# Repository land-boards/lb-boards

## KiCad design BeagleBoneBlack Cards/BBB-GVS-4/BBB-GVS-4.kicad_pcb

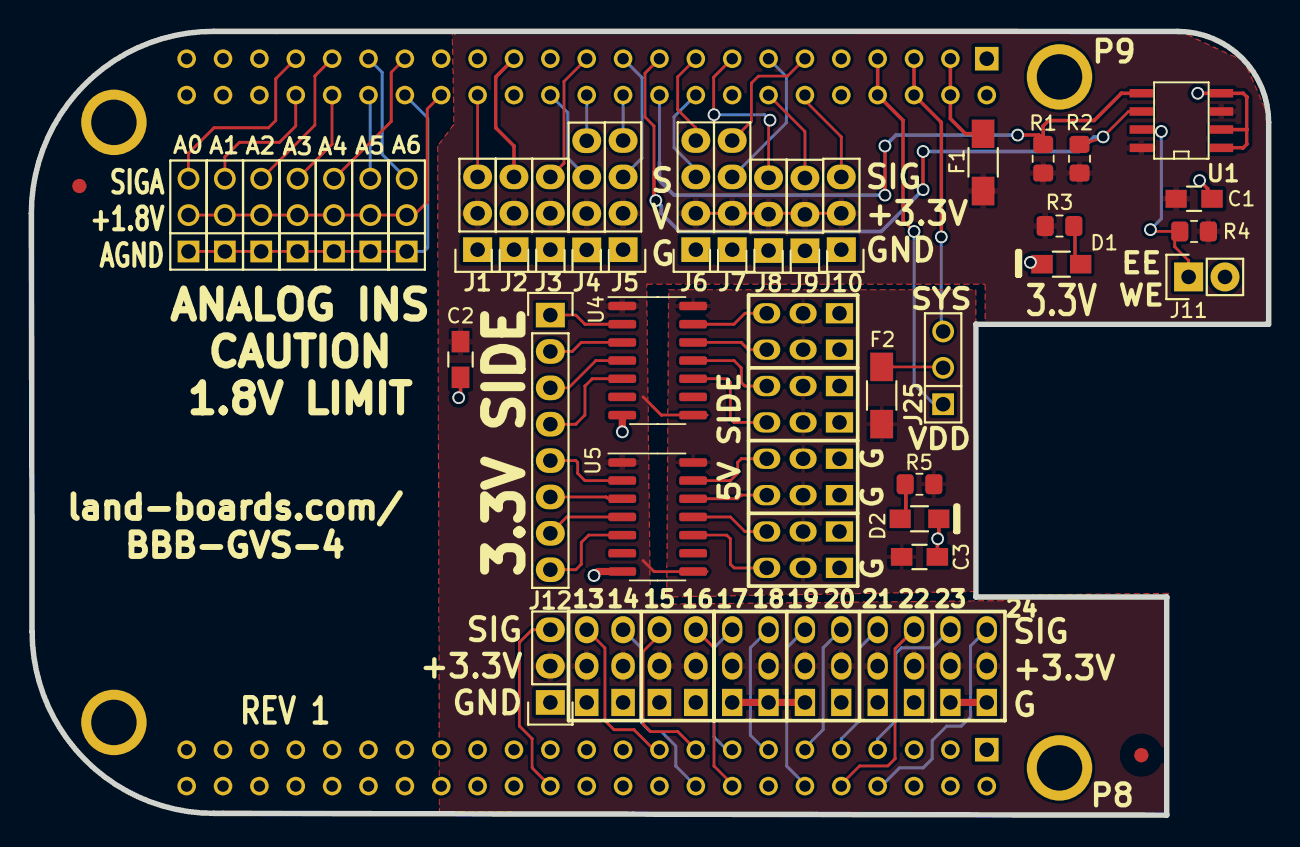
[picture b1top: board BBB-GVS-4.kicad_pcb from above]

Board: 2 copper layers, 86.4 x 54.7 mm, 43 parts (1 on the bottom side), 64 nets.

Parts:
A0, A1, A2, A3, A4, A5, A6: CONN_3; PIN_ARRAY_3X1
BRD1: BEAGLEBONE
C1: 1uF; C_0805_HandSoldering
C2, C3: 104; C_0805_HandSoldering
D1, D2: LED; R_0805_HandSoldering
F1, F2: FUSE; C_1206_HandSoldering
FID1, FID2: CONN_1; FIDUCIAL
J1, J2, J3, J8, J9, J10, J12: CONN_3; Pin_Header_Straight_1x03
J4, J5, J6, J7: CONN_4; Pin_Header_Straight_1x04
J11: CONN_2; Pin_Header_Straight_1x02
J16: GVS-4X3; Pin_Header_Straight_3x04
J24, J26: GVS-8X3; Pin_Header_Straight_3x08
J25: CONN_3; PIN_ARRAY_3X1
P1: CONN_8; Pin_Header_Straight_1x08
R1, R2, R4: 5.6K; R_0805_2012Metric_Pad1.20x1.40mm_HandSolder
R3: 120; R_0805_2012Metric_Pad1.20x1.40mm_HandSolder
R5: 330; R_0805_2012Metric_Pad1.20x1.40mm_HandSolder
TESTED: COUPON; REV_BLOCK
U1: I2C-EEPROM; SO8E-wider
U4, U5: TXS0104; SO-14_3.9x8.65mm_P1.27mm

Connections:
/BBB EEPROM Power Etc/F5VDD: F2.2, J25.2 (PM)
/P8 Connector/EHRPWM2A: BRD1.B19 (EHRPWM2A), J16.3
/P8 Connector/EHRPWM2B: BRD1.B13 (EHRPWM2B), J24.6
/P8 Connector/GPIO0_27: BRD1.B17 (GPIO0_27), J16.9
/P8 Connector/GPIO1_12: BRD1.B12 (GPIO1_12), J24.9
/P8 Connector/GPIO1_13: BRD1.B11 (GPIO1_13), J24.12
/P8 Connector/GPIO1_14: BRD1.B16 (GPIO1_14), J16.12
/P8 Connector/GPIO1_15: BRD1.B15 (GPIO1_15), J24.3
/P8 Connector/GPIO1_29: BRD1.B26 (GPIO1_29), J12.3
/P8 Connector/GPIO2_1: BRD1.B18 (GPIO2_1), J16.6
/P8 Connector/TIMER4: BRD1.B7 (TIMER4), J24.21
/P8 Connector/TIMER5: BRD1.B9 (TIMER5), J24.15
/P8 Connector/TIMER6: BRD1.B10 (TIMER6), J24.18
/P8 Connector/TIMER7: BRD1.B8 (TIMER7), J24.24
/P9 Connector/EHRPWM1A: BRD1.C14 (EHRPWM1A), J9.3
/P9 Connector/GPIO1_16: BRD1.C15 (GPIO1_16), J8.3
/P9 Connector/GPIO1_17: BRD1.C23 (GPIO1_17), J3.3
/P9 Connector/GPIO1_28: BRD1.C12 (GPIO1_28), J10.3
/P9 Connector/GPIO3_19: BRD1.C27 (GPIO3_19), J2.3
/P9 Connector/I2C1_SCL: BRD1.C17 (I2C1_SCL), J6.4
/P9 Connector/I2C1_SDA: BRD1.C18 (I2C1_SDA), J6.3
/P9 Connector/SPI1_D1: BRD1.C30 (SPI1_D1), J1.3
/P9 Connector/UART1_RXD: BRD1.C26 (UART1_RXD), J4.3
/P9 Connector/UART1_TXD: BRD1.C24 (UART1_TXD), J4.4
/P9 Connector/UART2_RXD: BRD1.C22 (UART2_RXD), J5.4
/P9 Connector/UART2_TXD: BRD1.C21 (UART2_TXD), J5.3
/P9 Connector/UART4_RXD: BRD1.C11 (UART4_RXD), J7.4
/P9 Connector/UART4_TXD: BRD1.C13 (UART4_TXD), J7.3
AIN0: A0.3, BRD1.C39 (AIN0)
AIN1: A1.3, BRD1.C40 (AIN1)
AIN2: A2.3, BRD1.C37 (AIN2)
AIN3: A3.3, BRD1.C38 (AIN3)
AIN4: A4.3, BRD1.C33 (AIN4)
AIN5: A5.3, BRD1.C36 (AIN5)
AIN6: A6.3, BRD1.C35 (AIN6)
GND: BRD1.B1 (DGND), BRD1.B2 (DGND), BRD1.C1 (DGND), BRD1.C2 (DGND), BRD1.C43 (DGND), BRD1.C44 (DGND), BRD1.C45 (DGND), BRD1.C46 (DGND), C1.2, C2.2, C3.2, D1.2 (K), D2.2 (K), J1.1, J2.1, J3.1, J4.1, J5.1, J6.1, J7.1, J8.1, J9.1, J10.1, J11.2 (PM), J12.1, J16.1 (G), J16.4, J16.7, J16.10, J24.1 (G), J24.4, J24.7, J24.10, J24.13, J24.16, J24.19, J24.22, J26.1 (G), J26.4, J26.7, J26.10, J26.13, J26.16, J26.19, J26.22, U1.1 (A0), U1.2 (A1), U1.4 (GND), U4.7 (GND), U5.7 (GND)
GNDA_ADC: A0.1, A1.1, A2.1, A3.1, A4.1, A5.1, A6.1, BRD1.C34 (GNDA_ADC)
I2C2_SCL: BRD1.C19 (I2C2_SCL), R2.2, U1.6 (SCL)
I2C2_SDA: BRD1.C20 (I2C2_SDA), R1.2, U1.5 (SDA)
unnamed: D1.1 (A), R3.2
unnamed: D2.1 (A), R5.2
unnamed: J11.1, R4.2, U1.7 (WP)
unnamed: J26.3, U5.10 (B4)
unnamed: J26.6, U5.11 (B3)
unnamed: J26.9, U5.12 (B2)
unnamed: J26.12, U5.13 (B1)
unnamed: J26.15, U4.10 (B4)
unnamed: J26.18, U4.11 (B3)
unnamed: J26.21, U4.12 (B2)
unnamed: J26.24, U4.13 (B1)
unnamed: P1.1, U4.2 (A1)
unnamed: P1.2, U4.3 (A2)
unnamed: P1.3, U4.4 (A3)
unnamed: P1.4, U4.5 (A4)
unnamed: P1.5, U5.2 (A1)
unnamed: P1.6, U5.3 (A2)
unnamed: P1.7, U5.4 (A3)
unnamed: P1.8, U5.5 (A4)
SYS_5V: BRD1.C7 (SYS_5V), BRD1.C8 (SYS_5V), J25.1
VCC_3V3EXP: C1.1, C2.1, F1.1, J1.2 (PM), J2.2 (PM), J3.2 (PM), J4.2, J5.2, J6.2, J7.2, J8.2 (PM), J9.2 (PM), J10.2 (PM), J12.2 (PM), J16.2 (V), J16.5, J16.8, J16.11, J24.2 (V), J24.5, J24.8, J24.11, J24.14, J24.17, J24.20, J24.23, R1.1, R2.1, R3.1, R4.1, U1.3 (A2), U1.8 (VCC), U4.1 (VCCA(LV)), U4.8 (OE), U5.1 (VCCA(LV)), U5.8 (OE)
VDD_3V3-UF: BRD1.C3 (VDD_3V3EXP), BRD1.C4 (VDD_3V3EXP), F1.2
VDD_5V: C3.1, F2.1, J26.2 (V), J26.5, J26.8, J26.11, J26.14, J26.17, J26.20, J26.23, R5.1, U4.14 (VCCB(HV)), U5.14 (VCCB(HV))
VDD_5V-UF: BRD1.C5 (VDD_5V), BRD1.C6 (VDD_5V), J25.3
VDD_ADC: A0.2 (PM), A1.2 (PM), A2.2 (PM), A3.2 (PM), A4.2 (PM), A5.2 (PM), A6.2 (PM), BRD1.C32 (VDD_ADC)

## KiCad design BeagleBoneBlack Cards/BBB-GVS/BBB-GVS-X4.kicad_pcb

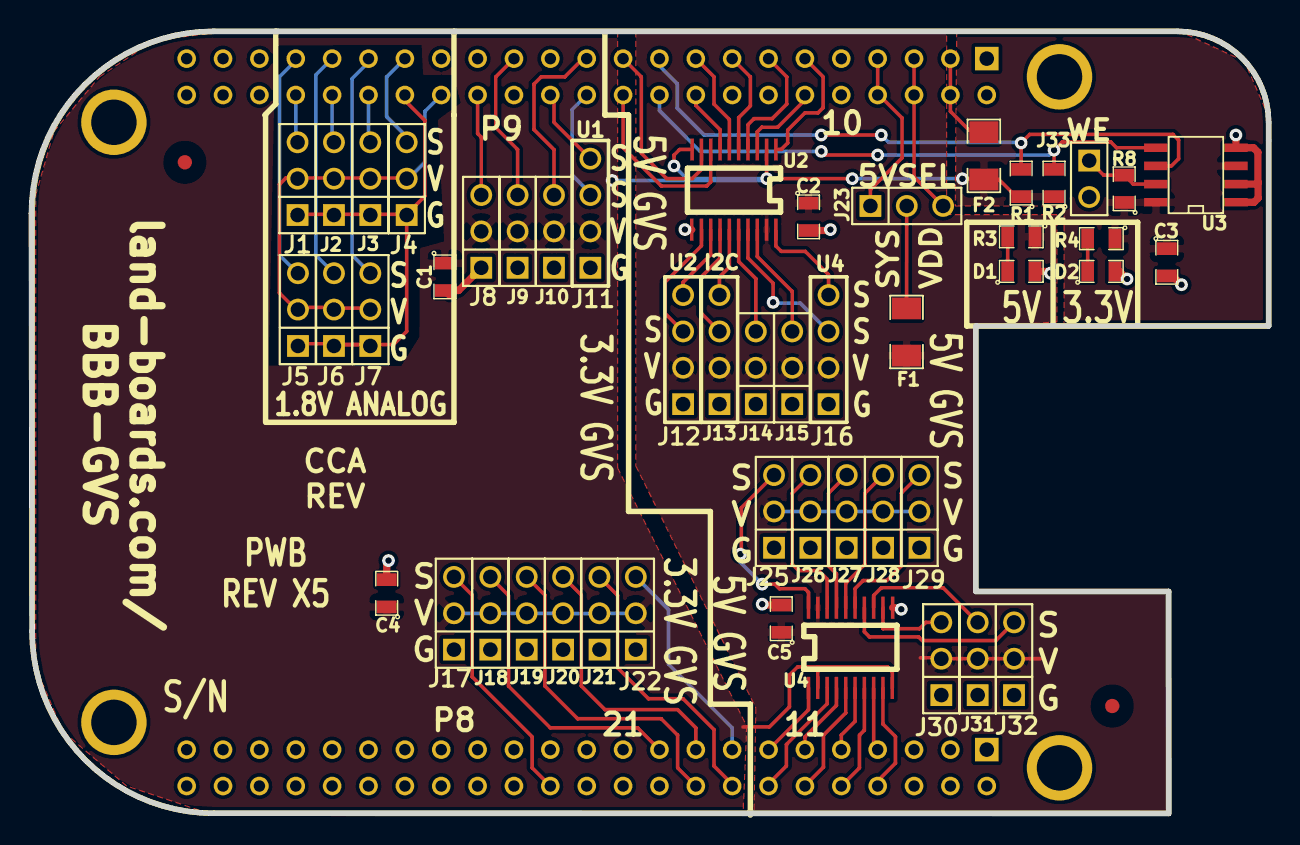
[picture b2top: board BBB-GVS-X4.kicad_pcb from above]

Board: 2 copper layers, 86.4 x 54.6 mm, 52 parts (0 on the bottom side), 64 nets.

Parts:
BRD1: BEAGLEBONE
C1, C2, C4, C5: 104; SM0805
C3: 1uF; SM0805
D1, D2: LED; SM0805
F1, F2: FUSE; SM1206
FID1, FID2: CONN_1; FIDUCIAL
J1, J2, J3, J4, J5, J6, J7, J8, J9, J10, J14, J15, J17, J18, J19, J20, J21, J22, J23, J25, J26, J27, J28, J29, J30, J31, J32: CONN_3; PIN_ARRAY_3X1
J11, J12, J13, J16: CONN_4; PIN_ARRAY_4x1
J33: CONN_2; PIN_ARRAY_2X1
R1, R2, R8: 5.6K; SM0805
R3: 330; SM0805
R4: 120; SM0805
U2: TXB0108EPWR; SOG20
U3: CAT24C256; SO8E-wider
U4: TXS0108EPWR; SOG20

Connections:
/P8 Connector/EHRPWM2A: BRD1.B19, J18.3
/P8 Connector/EHRPWM2B: BRD1.B13, U4.1
/P8 Connector/GP0_26: J26.3, U4.18
/P8 Connector/GP1_12: J28.3, U4.16
/P8 Connector/GP1_13: J27.3, U4.17
/P8 Connector/GPIO0_26: BRD1.B14, U4.3
/P8 Connector/GPIO0_27: BRD1.B17, J20.3
/P8 Connector/GPIO1_12: BRD1.B12, U4.5
/P8 Connector/GPIO1_13: BRD1.B11, U4.4
/P8 Connector/GPIO1_14: BRD1.B16, J21.3
/P8 Connector/GPIO1_15: BRD1.B15, J22.3
/P8 Connector/GPIO1_29: BRD1.B26, J17.3
/P8 Connector/GPIO2_1: BRD1.B18, J19.3
/P8 Connector/PWM2B: J25.3, U4.20
/P8 Connector/TIM4: J31.3, U4.13
/P8 Connector/TIM5: J29.3, U4.15
/P8 Connector/TIM6: J32.3, U4.14
/P8 Connector/TIM7: J30.3, U4.12
/P8 Connector/TIMER4: BRD1.B7, U4.8
/P8 Connector/TIMER5: BRD1.B9, U4.6
/P8 Connector/TIMER6: BRD1.B10, U4.7
/P8 Connector/TIMER7: BRD1.B8, U4.9
/P9 Connector/AIN0: BRD1.C39, J5.3
/P9 Connector/AIN1: BRD1.C40, J1.3
/P9 Connector/AIN2: BRD1.C37, J6.3
/P9 Connector/AIN3: BRD1.C38, J2.3
/P9 Connector/AIN4: BRD1.C33, J4.3
/P9 Connector/AIN5: BRD1.C36, J3.3
/P9 Connector/AIN6: BRD1.C35, J7.3
/P9 Connector/GNDA_ADC: BRD1.C34, J1.1, J2.1, J3.1, J4.1, J5.1, J6.1, J7.1
/P9 Connector/GP1_28: J15.3, U2.18
/P9 Connector/GP116: J14.3, U2.16
/P9 Connector/GPIO1_16: BRD1.C15, U2.5
/P9 Connector/GPIO1_17: BRD1.C23, J10.3
/P9 Connector/GPIO1_28: BRD1.C12, U2.3
/P9 Connector/GPIO3_19: BRD1.C27, J9.3
/P9 Connector/I2C1CL: J13.4, U2.15
/P9 Connector/I2C1SD: J13.3, U2.14
/P9 Connector/I2C1_SCL: BRD1.C17, U2.6
/P9 Connector/I2C1_SDA: BRD1.C18, U2.7
/P9 Connector/I2C2_SCL: BRD1.C19, R1.2, U3.6
/P9 Connector/I2C2_SDA: BRD1.C20, R2.2, U3.5
/P9 Connector/SPI1_D1: BRD1.C30, J8.3
/P9 Connector/SYS_5V: BRD1.C7, BRD1.C8, J23.1
/P9 Connector/U2RX: J12.4, U2.13
/P9 Connector/U2TX: J12.3, U2.12
/P9 Connector/U4RX: J16.4, U2.20
/P9 Connector/U4TX: J16.3, U2.17
/P9 Connector/UART1_RXD: BRD1.C26, J11.4
/P9 Connector/UART1_TXD: BRD1.C24, J11.3
/P9 Connector/UART2_RXD: BRD1.C22, U2.8
/P9 Connector/UART2_TXD: BRD1.C21, U2.9
/P9 Connector/UART4_RXD: BRD1.C11, U2.1
/P9 Connector/UART4_TXD: BRD1.C13, U2.4
/P9 Connector/VDD_3V3-UF: BRD1.C3, BRD1.C4, F2.2
/P9 Connector/VDD_ADC: BRD1.C32, J1.2, J2.2, J3.2, J4.2, J5.2, J6.2, J7.2
GND: BRD1.B1, BRD1.B2, BRD1.C1, BRD1.C2, BRD1.C43, BRD1.C44, BRD1.C45, BRD1.C46, C1.2, C2.2, C3.2, C4.2, C5.2, D1.2, D2.2, J8.1, J9.1, J10.1, J11.1, J12.1, J13.1, J14.1, J15.1, J16.1, J17.1, J18.1, J19.1, J20.1, J21.1, J22.1, J25.1, J26.1, J27.1, J28.1, J29.1, J30.1, J31.1, J32.1, J33.2, U2.11, U3.1, U3.2, U3.4, U4.11
unnamed: D1.1, R3.2
unnamed: D2.1, R4.2
unnamed: F1.2, J23.2
unnamed: J33.1, R8.2, U3.7
VDD_3V3EXP: C1.1, C3.1, C4.1, F2.1, J8.2, J9.2, J10.2, J11.2, J17.2, J18.2, J19.2, J20.2, J21.2, J22.2, R1.1, R2.1, R4.1, R8.1, U2.2, U2.10, U3.3, U3.8, U4.2, U4.10
VDD_5V: C2.1, C5.1, F1.1, J12.2, J13.2, J14.2, J15.2, J16.2, J25.2, J26.2, J27.2, J28.2, J29.2, J30.2, J31.2, J32.2, R3.1, U2.19, U4.19
VDD_5V-UF: BRD1.C5, BRD1.C6, J23.3

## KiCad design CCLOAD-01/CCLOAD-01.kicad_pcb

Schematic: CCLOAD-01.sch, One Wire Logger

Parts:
C1, C7: 0.1uF; C_0805_HandSoldering
C2, C6: 10uF; C_1210_HandSoldering
C3: 0.1; C_0805_HandSoldering
COUP1: COUPON; Fiducial_1mm_Dia_2.54mm_Outer_CopperTop
COUP2: COUPON; TEST_BLK-REAR
COUP?1: COUPON; Fiducial_1mm_Dia_2.54mm_Outer_CopperTop
J1: DCJ0202; DCJ-NEW
MTG1, MTG2, MTG3, MTG4: COUPON; MTG-4-40
P1, P6, P7: CONN_01X03; Pin_Header_Straight_1x03
P2, P3: CONN_01X01; MTG-4-40
P4: CONN_01X02; Pin_Header_Straight_1x02
Q1: BTS117; TO-220_Neutral123_Vertical
R1, R4, R6, R7, R8: 10K; R_0805_HandSoldering
R2: 90.9K; R_0805_HandSoldering
R3: 100; R_0805_HandSoldering
R5: 0.05; R_2512_HandSoldering
R9: 000; R_0805_HandSoldering
R10: DNP; R_0805_HandSoldering
R11: 162K; R_0805_HandSoldering
RV2: 1K; Potentiometer_Bourns_3296W_3-8Zoll_Inline_ScrewUp
U1: LM324AN; SOIC-14_3.9x8.7mm_Pitch1.27mm
U2: MCP6002; SOIC-8_3.9x4.9mm_Pitch1.27mm
U3: LM2936MP; SOT-223

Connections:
+9V: C1.1, C2.1, J1.1, P6.3, P7.3, U1.4 (V+), U3.1 (VIN)
/GO: P1.2, U2.3 (+)
/ID10: R7.2, R8.2, U2.7 (Q)
/IDPRT: R8.1, U1.3 (+)
/IMET: P7.2, R2.2, U1.1
/IMFB: R1.1, R2.1, U1.2 (-)
/IOFF: RV2.2, U2.6 (-)
/ISENS: Q1.3 (S), R4.1, R5.2, U2.5 (+)
/VG: Q1.1 (G), R3.1
/VGOP: C3.1, R3.2, U2.1 (Q)
/VLOAD: P2.1, Q1.2 (D), R9.2
GND: C1.2, C2.2, C6.2, C7.2, J1.2, J1.3, P1.1, P3.1, P4.1, P6.1, P7.1, R1.2, R5.1, R6.2, R10.1, U1.11 (V-), U2.4 (VSS), U3.2 (VO), U3.4 (GND)
unnamed: C3.2, R4.2, U2.2 (-)
unnamed: P1.3, R11.1
unnamed: P6.2, R9.1, R10.2
unnamed: R6.1, RV2.3
unnamed: R7.1, RV2.1
VDD: C6.1, C7.1, P4.2, R11.2, U2.8 (VDD), U3.3 (VO)

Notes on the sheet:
VOLTMETER DISPLAYS VOLTS
VOLTMETER DISPLAYS AMPS
Load Current Adjust
Load Transistor

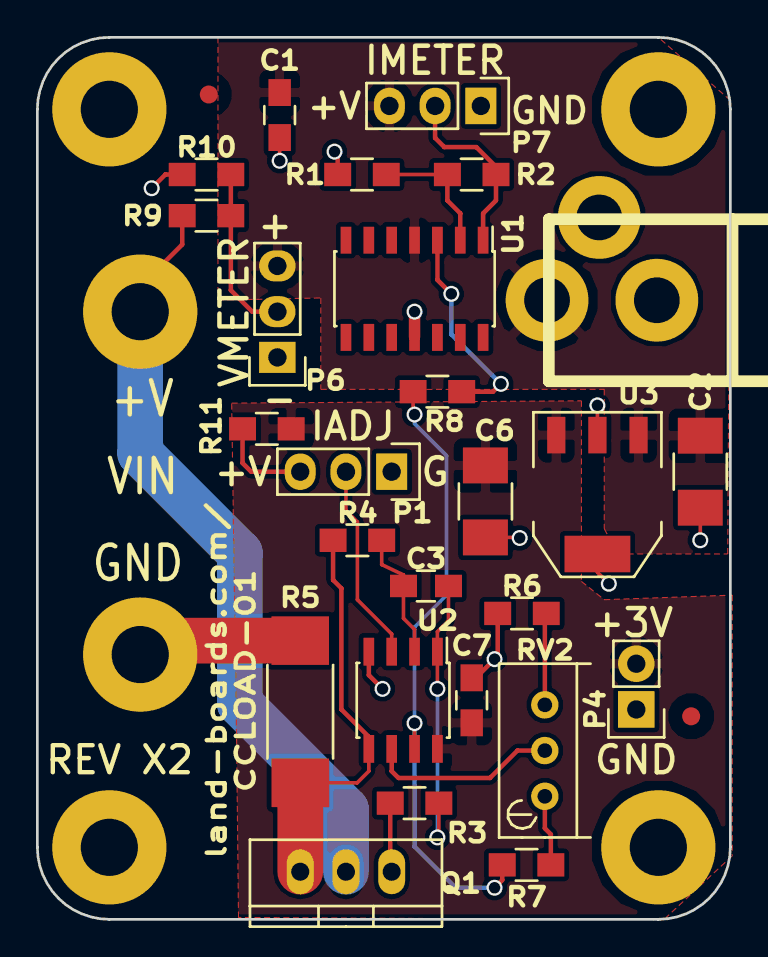
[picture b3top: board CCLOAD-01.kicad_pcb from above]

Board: 2 copper layers, 38.5 x 49.0 mm, 35 parts (0 on the bottom side), 18 nets.

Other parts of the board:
TESTED: VAL**; TEST_BLK-REAR

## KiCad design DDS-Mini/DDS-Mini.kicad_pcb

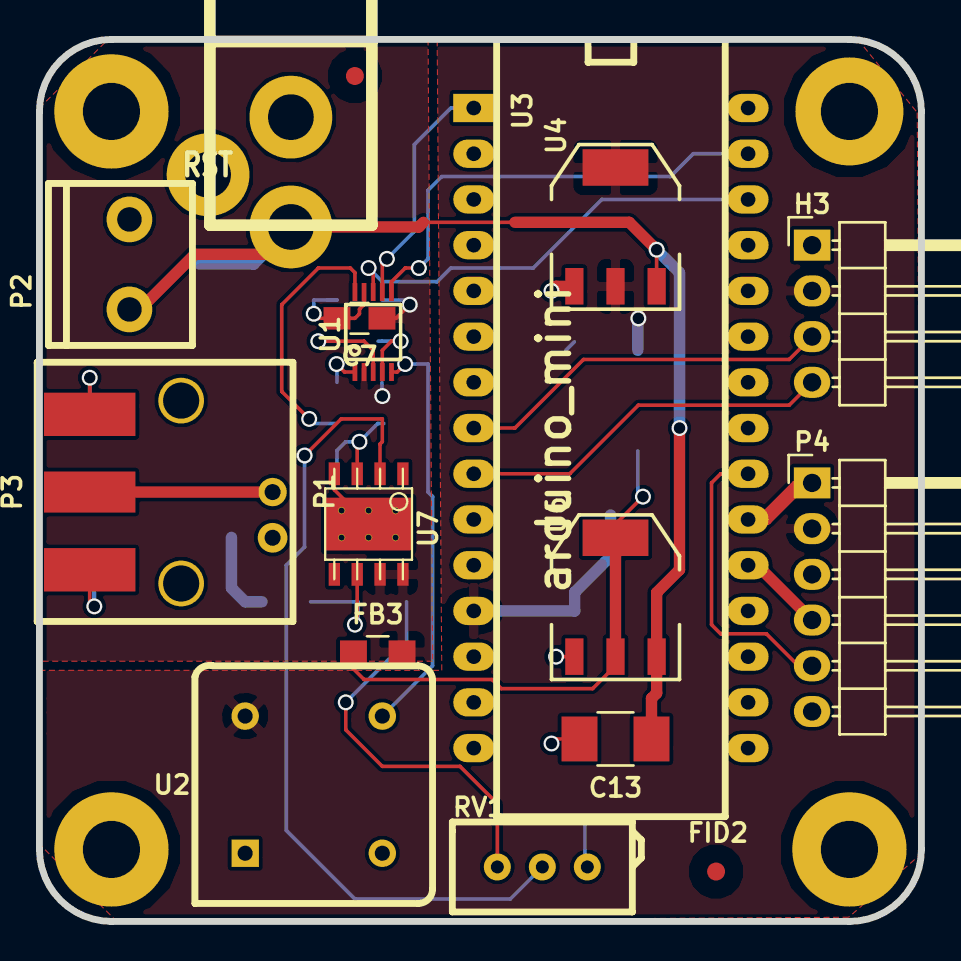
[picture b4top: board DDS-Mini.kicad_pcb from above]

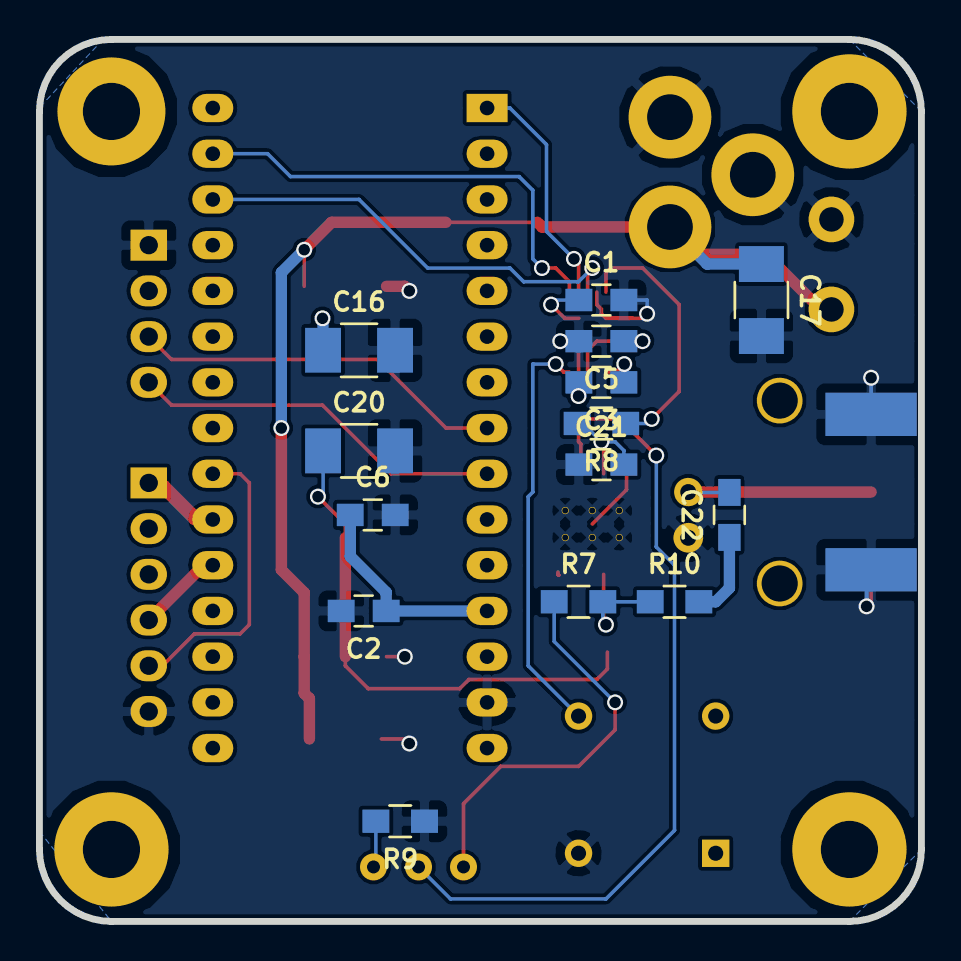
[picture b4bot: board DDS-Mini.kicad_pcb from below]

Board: 2 copper layers, 49.0 x 49.0 mm, 36 parts (14 on the bottom side), 24 nets.

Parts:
C1, C2, C6, C7: 0.1uF; C_0805_HandSoldering
C3, C5: 10nF; C_0805_HandSoldering
C13, C17: 10uF; C_1210_HandSoldering
C16, C20: 1uF; C_1210_HandSoldering
C21: 10pF; C_0805_HandSoldering
C22: .33uF; C_0805_HandSoldering
FB3: MPZ2012S101A; R_0805_HandSoldering
FID1, FID2: CONN_1; FIDUCIAL
H3: CONN_4; Pin_Header_Angled_1x04
J1: DCJ0202; DCJ-NEW
MTG1, MTG2, MTG3, MTG4: CONN_1; MTG-4-40
P1: BNC; BNC-RT
P2: CONN_2; TB2-5MM
P3: CONN_2; SMA_EDGE
P4: CONN_01X06; Pin_Header_Angled_1x06
R7: 510K; R_0805_HandSoldering
R8: 20; R_0805_HandSoldering
R9: 82K; R_0805_HandSoldering
R10: 001; R_0805_HandSoldering
RV1: 100K; POT-5X10MM
U1: AD9833; MSOP10-0.5
U2: 25.000MHz; OSC-ACHL
U3: arduino_mini
U4, U6: TLV1117-50CDCYR; SOT223
U7: OPA357-MSOP8; HSOP-8

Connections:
/Analog/Digital LDOs/AVDD: C1.1, C3.2, C7.1, FB3.2, U1.2, U7.7, U7.8
/Analog/Digital LDOs/DVDD: C2.1, C6.1, C16.1, H3.2, P4.2, U2.8, U3.12, U4.2, U4.4
/Analog/Digital LDOs/VAOUT: C20.1, FB3.1, U6.2, U6.4
/Analog/Digital LDOs/VIN: C13.1, C17.1, J1.1, P2.1, U4.3, U6.3
/Buffer Amplifier/AGND: C1.2, C2.2, C5.2, C6.2, C7.2, C13.2, C16.2, C17.2, C20.2, C21.1, H3.1, J1.2, J1.3, P1.2, P2.2, P3.2, P4.6, R9.1, U1.4, U1.9, U2.4, U3.14, U4.1, U6.1, U7.4, U7.9
/Buffer Amplifier/AO: R7.2, R10.1, U7.6
/Buffer Amplifier/RF-IN: R8.1, U1.10
/Buffer Amplifier/RF-OUT: C22.2, P1.1, P3.1
/DDS/DDS-~CS: U1.8, U3.28
/DDS/MCLK: U1.5, U2.5
/DDS/REFCAP: C5.1, U1.3
/Microprocessor/DDS-MOSI: U1.6, U3.29
/Microprocessor/DDS-SCK: U1.7, U3.1
unnamed: C3.1, U1.1
unnamed: C21.2, R8.2, U7.3
unnamed: C22.1, R10.2
unnamed: H3.3, U3.8
unnamed: H3.4, U3.9
unnamed: P4.1, U3.21
unnamed: P4.4, U3.20
unnamed: P4.5, U3.22
unnamed: R7.1, RV1.1
unnamed: R9.2, RV1.3
unnamed: RV1.2, U7.2

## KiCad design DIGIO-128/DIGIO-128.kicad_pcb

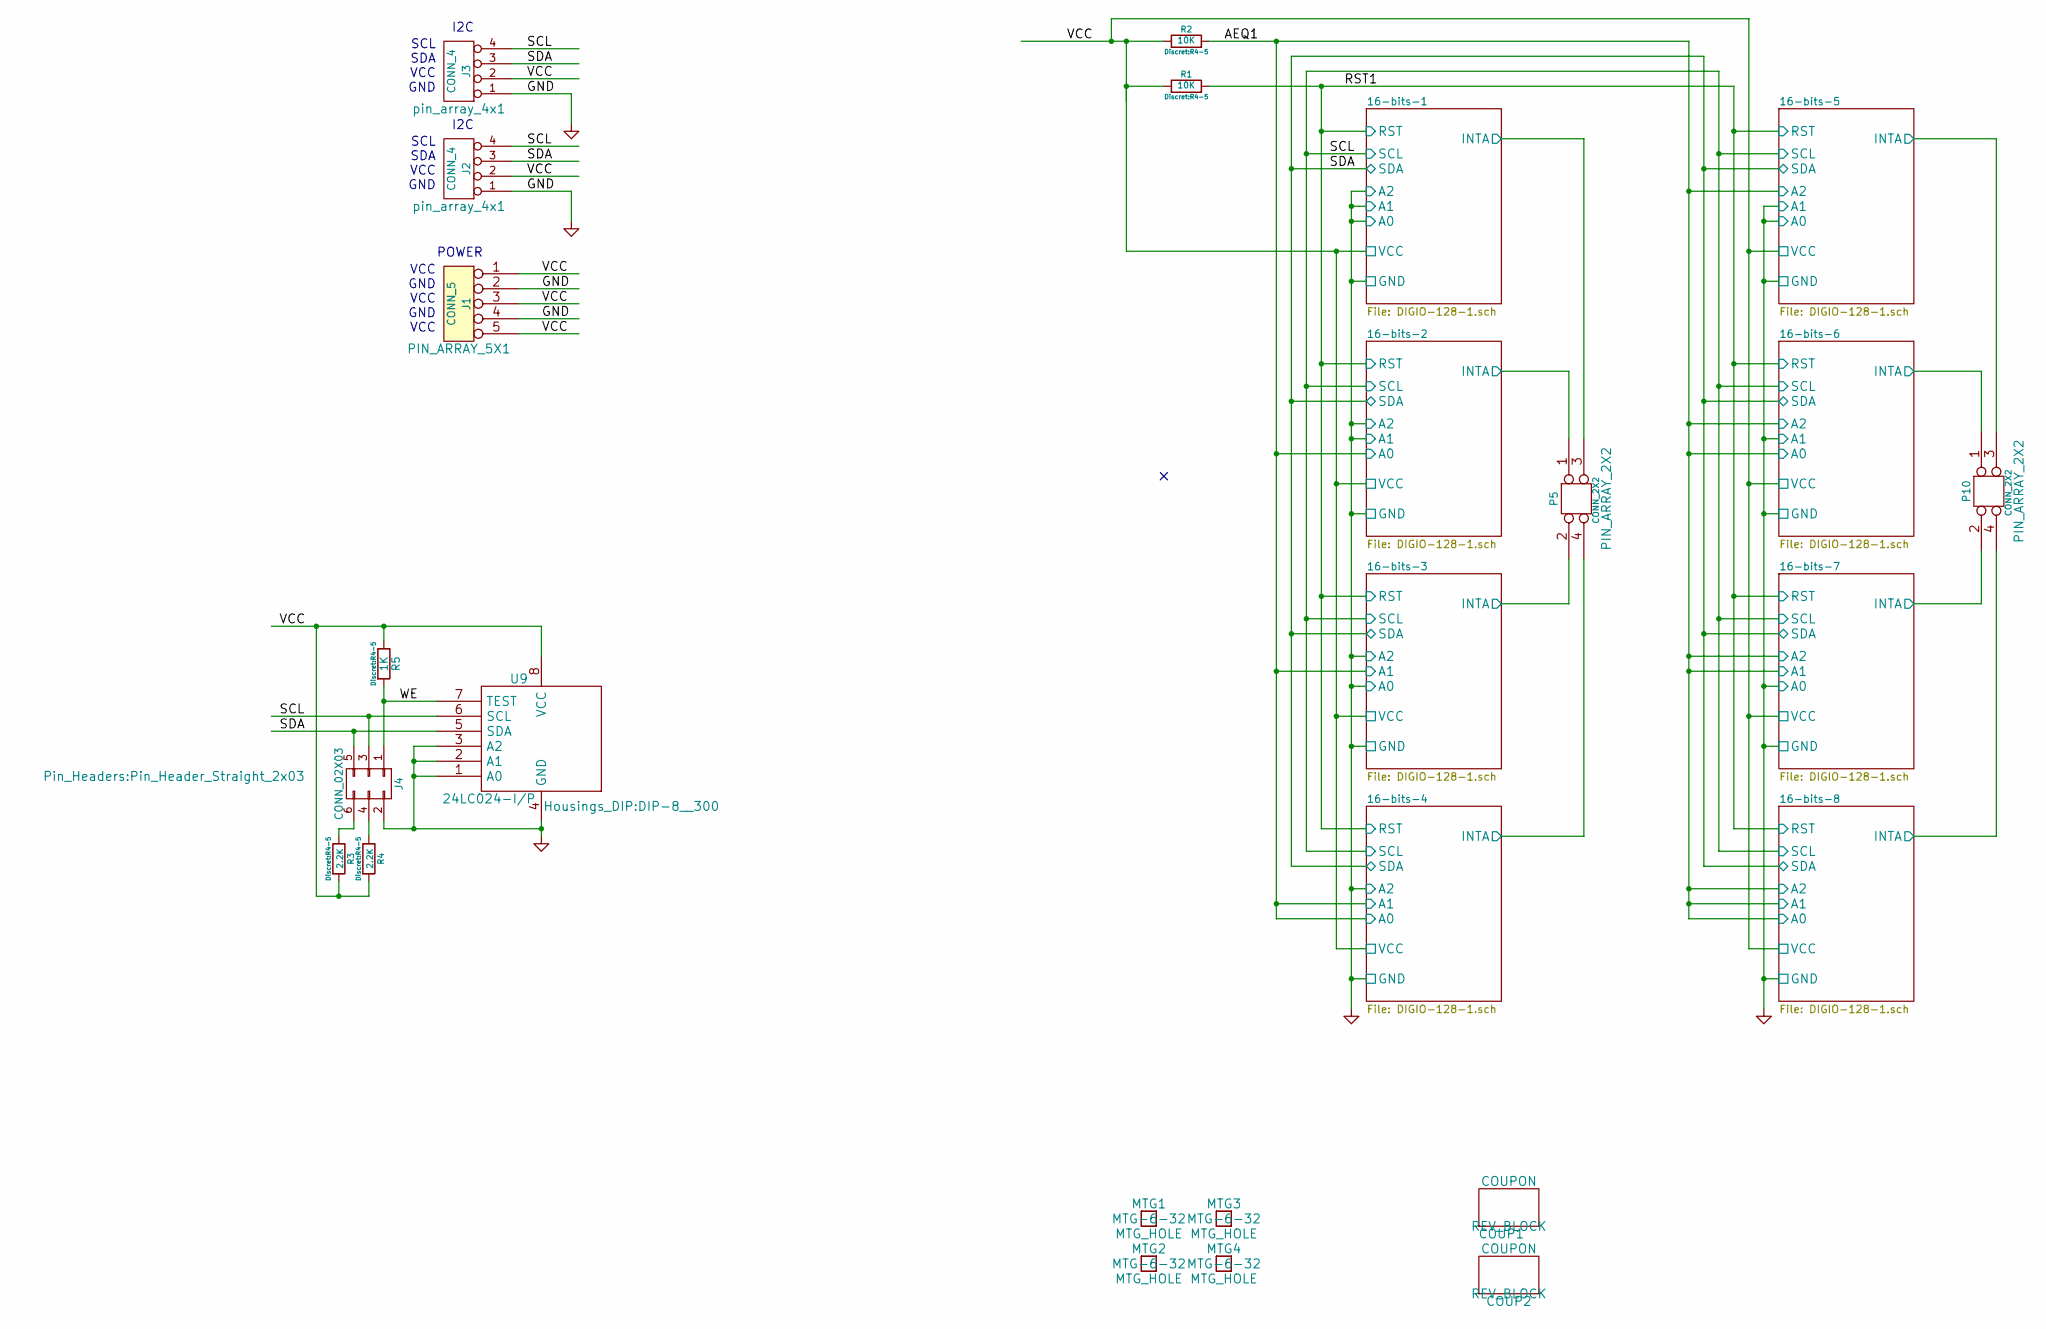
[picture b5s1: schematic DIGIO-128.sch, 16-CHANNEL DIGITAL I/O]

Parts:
COUP1, COUP2: COUPON; REV_BLOCK
J1: CONN_5; PIN_ARRAY_5X1
J2, J3: CONN_4; pin_array_4x1
J4: CONN_02X03; Pin_Header_Straight_2x03
MTG1, MTG2, MTG3, MTG4: MTG_HOLE; MTG-6-32
P5, P10: CONN_2X2; PIN_ARRAY_2X2
R1, R2: 10K; R4-5
R3, R4: 2.2K; R4-5
R5: 1K; R4-5
U9: 24LC024-I/P; DIP-8__300

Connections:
/16-bits-1/INTA: P5.3; also elsewhere on the board
/16-bits-1/RST: R1.2; also elsewhere on the board
/16-bits-1/SCL: J2.4, J3.4, J4.3, U9.6 (SCL); also elsewhere on the board
/16-bits-1/SDA: J2.3, J3.3, J4.5, U9.5 (SDA); also elsewhere on the board
/16-bits-1/VCC: J1.1, J1.3, J1.5, J2.2, J3.2, R1.1, R2.1, R3.2, R4.2, R5.1, U9.8 (VCC); also elsewhere on the board
/16-bits-2/A0: R2.2; also elsewhere on the board
/16-bits-2/INTA: P5.1; also elsewhere on the board
/16-bits-3/INTA: P5.2; also elsewhere on the board
/16-bits-4/INTA: P5.4; also elsewhere on the board
/16-bits-5/INTA: P10.3; also elsewhere on the board
/16-bits-6/INTA: P10.1; also elsewhere on the board
/16-bits-7/INTA: P10.2; also elsewhere on the board
/16-bits-8/INTA: P10.4; also elsewhere on the board
/WE: J4.1, R5.2, U9.7 (TEST)
GND: J1.2, J1.4, J2.1, J3.1, J4.2, U9.1 (A0), U9.2 (A1), U9.3 (A2), U9.4 (GND); also elsewhere on the board
unnamed: J4.4, R4.1
unnamed: J4.6, R3.1

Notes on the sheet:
SCL SDA VCC GND
VCC GND VCC GND VCC
POWER
I2C

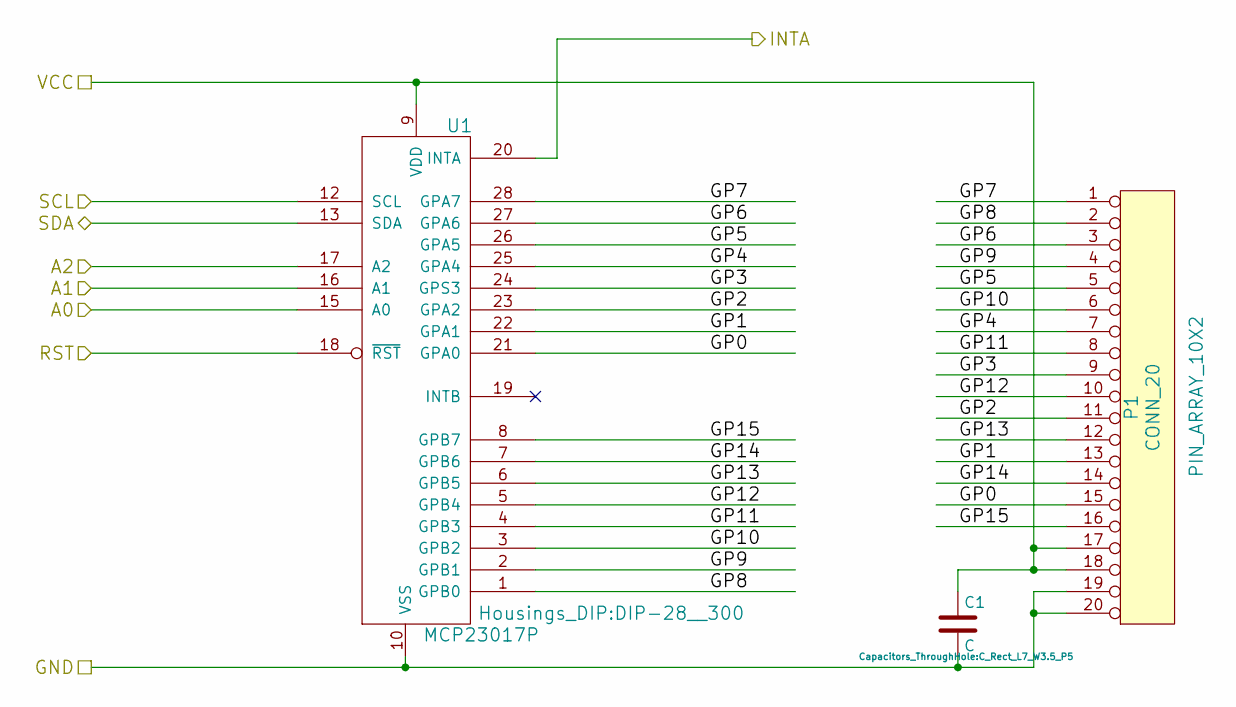
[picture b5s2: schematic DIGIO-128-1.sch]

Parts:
C1: C; C_Rect_L7_W3.5_P5
P1: CONN_20; PIN_ARRAY_10X2
U1: MCP23017P; DIP-28__300

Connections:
/16-bits-1/GP0: P1.15, U1.21 (GPA0)
/16-bits-1/GP1: P1.13, U1.22 (GPA1)
/16-bits-1/GP2: P1.11, U1.23 (GPA2)
/16-bits-1/GP3: P1.9, U1.24 (GPS3)
/16-bits-1/GP4: P1.7, U1.25 (GPA4)
/16-bits-1/GP5: P1.5, U1.26 (GPA5)
/16-bits-1/GP6: P1.3, U1.27 (GPA6)
/16-bits-1/GP7: P1.1, U1.28 (GPA7)
/16-bits-1/GP8: P1.2, U1.1 (GPB0)
/16-bits-1/GP9: P1.4, U1.2 (GPB1)
/16-bits-1/GP10: P1.6, U1.3 (GPB2)
/16-bits-1/GP11: P1.8, U1.4 (GPB3)
/16-bits-1/GP12: P1.10, U1.5 (GPB4)
/16-bits-1/GP13: P1.12, U1.6 (GPB5)
/16-bits-1/GP14: P1.14, U1.7 (GPB6)
/16-bits-1/GP15: P1.16, U1.8 (GPB7)
/16-bits-1/INTA: U1.20 (INTA); also elsewhere on the board
/16-bits-1/RST: U1.18 (~RST); also elsewhere on the board
/16-bits-1/SCL: U1.12 (SCL); also elsewhere on the board
/16-bits-1/SDA: U1.13 (SDA); also elsewhere on the board
/16-bits-1/VCC: C1.1, P1.17, P1.18, U1.9 (VDD); also elsewhere on the board
GND: C1.2, P1.19, P1.20, U1.10 (VSS), U1.15 (A0), U1.16 (A1), U1.17 (A2); also elsewhere on the board

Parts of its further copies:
C2, C3, C4, C5, C6, C7, C8: C; C_Rect_L7_W3.5_P5
P2, P3, P4, P6, P7, P8, P9: CONN_20; PIN_ARRAY_10X2
U2, U3, U4, U5, U6, U7, U8: MCP23017P; DIP-28__300

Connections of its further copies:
/16-bits-1/RST: U2.18 (~RST), U3.18 (~RST), U4.18 (~RST), U5.18 (~RST), U6.18 (~RST), U7.18 (~RST), U8.18 (~RST); also elsewhere on the board
/16-bits-1/SCL: U2.12 (SCL), U3.12 (SCL), U4.12 (SCL), U5.12 (SCL), U6.12 (SCL), U7.12 (SCL), U8.12 (SCL); also elsewhere on the board
/16-bits-1/SDA: U2.13 (SDA), U3.13 (SDA), U4.13 (SDA), U5.13 (SDA), U6.13 (SDA), U7.13 (SDA), U8.13 (SDA); also elsewhere on the board
/16-bits-1/VCC: C2.1, C3.1, C4.1, C5.1, C6.1, C7.1, C8.1, P2.17, P2.18, P3.17, P3.18, P4.17, P4.18, P6.17, P6.18, P7.17, P7.18, P8.17, P8.18, P9.17, P9.18, U2.9 (VDD), U3.9 (VDD), U4.9 (VDD), U5.9 (VDD), U6.9 (VDD), U7.9 (VDD), U8.9 (VDD); also elsewhere on the board
/16-bits-2/A0: U2.15 (A0), U3.16 (A1), U4.15 (A0), U4.16 (A1), U5.17 (A2), U6.15 (A0), U6.17 (A2), U7.16 (A1), U7.17 (A2), U8.15 (A0), U8.16 (A1), U8.17 (A2); also elsewhere on the board
/16-bits-2/GP0: P2.15, U2.21 (GPA0)
/16-bits-2/GP1: P2.13, U2.22 (GPA1)
/16-bits-2/GP2: P2.11, U2.23 (GPA2)
/16-bits-2/GP3: P2.9, U2.24 (GPS3)
/16-bits-2/GP4: P2.7, U2.25 (GPA4)
/16-bits-2/GP5: P2.5, U2.26 (GPA5)
/16-bits-2/GP6: P2.3, U2.27 (GPA6)
/16-bits-2/GP7: P2.1, U2.28 (GPA7)
/16-bits-2/GP8: P2.2, U2.1 (GPB0)
/16-bits-2/GP9: P2.4, U2.2 (GPB1)
/16-bits-2/GP10: P2.6, U2.3 (GPB2)
/16-bits-2/GP11: P2.8, U2.4 (GPB3)
/16-bits-2/GP12: P2.10, U2.5 (GPB4)
/16-bits-2/GP13: P2.12, U2.6 (GPB5)
/16-bits-2/GP14: P2.14, U2.7 (GPB6)
/16-bits-2/GP15: P2.16, U2.8 (GPB7)
/16-bits-2/INTA: U2.20 (INTA); also elsewhere on the board
/16-bits-3/GP0: P3.15, U3.21 (GPA0)
/16-bits-3/GP1: P3.13, U3.22 (GPA1)
/16-bits-3/GP2: P3.11, U3.23 (GPA2)
/16-bits-3/GP3: P3.9, U3.24 (GPS3)
/16-bits-3/GP4: P3.7, U3.25 (GPA4)
/16-bits-3/GP5: P3.5, U3.26 (GPA5)
/16-bits-3/GP6: P3.3, U3.27 (GPA6)
/16-bits-3/GP7: P3.1, U3.28 (GPA7)
/16-bits-3/GP8: P3.2, U3.1 (GPB0)
/16-bits-3/GP9: P3.4, U3.2 (GPB1)
/16-bits-3/GP10: P3.6, U3.3 (GPB2)
/16-bits-3/GP11: P3.8, U3.4 (GPB3)
/16-bits-3/GP12: P3.10, U3.5 (GPB4)
/16-bits-3/GP13: P3.12, U3.6 (GPB5)
/16-bits-3/GP14: P3.14, U3.7 (GPB6)
/16-bits-3/GP15: P3.16, U3.8 (GPB7)
/16-bits-3/INTA: U3.20 (INTA); also elsewhere on the board
/16-bits-4/GP0: P4.15, U4.21 (GPA0)
/16-bits-4/GP1: P4.13, U4.22 (GPA1)
/16-bits-4/GP2: P4.11, U4.23 (GPA2)
/16-bits-4/GP3: P4.9, U4.24 (GPS3)
/16-bits-4/GP4: P4.7, U4.25 (GPA4)
/16-bits-4/GP5: P4.5, U4.26 (GPA5)
/16-bits-4/GP6: P4.3, U4.27 (GPA6)
/16-bits-4/GP7: P4.1, U4.28 (GPA7)
/16-bits-4/GP8: P4.2, U4.1 (GPB0)
/16-bits-4/GP9: P4.4, U4.2 (GPB1)
/16-bits-4/GP10: P4.6, U4.3 (GPB2)
/16-bits-4/GP11: P4.8, U4.4 (GPB3)
/16-bits-4/GP12: P4.10, U4.5 (GPB4)
/16-bits-4/GP13: P4.12, U4.6 (GPB5)
/16-bits-4/GP14: P4.14, U4.7 (GPB6)
/16-bits-4/GP15: P4.16, U4.8 (GPB7)
/16-bits-4/INTA: U4.20 (INTA); also elsewhere on the board
/16-bits-5/GP0: P6.15, U5.21 (GPA0)
/16-bits-5/GP1: P6.13, U5.22 (GPA1)
/16-bits-5/GP2: P6.11, U5.23 (GPA2)
/16-bits-5/GP3: P6.9, U5.24 (GPS3)
/16-bits-5/GP4: P6.7, U5.25 (GPA4)
/16-bits-5/GP5: P6.5, U5.26 (GPA5)
/16-bits-5/GP6: P6.3, U5.27 (GPA6)
/16-bits-5/GP7: P6.1, U5.28 (GPA7)
/16-bits-5/GP8: P6.2, U5.1 (GPB0)
/16-bits-5/GP9: P6.4, U5.2 (GPB1)
/16-bits-5/GP10: P6.6, U5.3 (GPB2)
/16-bits-5/GP11: P6.8, U5.4 (GPB3)
/16-bits-5/GP12: P6.10, U5.5 (GPB4)
/16-bits-5/GP13: P6.12, U5.6 (GPB5)
/16-bits-5/GP14: P6.14, U5.7 (GPB6)
/16-bits-5/GP15: P6.16, U5.8 (GPB7)
/16-bits-5/INTA: U5.20 (INTA); also elsewhere on the board
/16-bits-6/GP0: P7.15, U6.21 (GPA0)
/16-bits-6/GP1: P7.13, U6.22 (GPA1)
/16-bits-6/GP2: P7.11, U6.23 (GPA2)
/16-bits-6/GP3: P7.9, U6.24 (GPS3)
/16-bits-6/GP4: P7.7, U6.25 (GPA4)
/16-bits-6/GP5: P7.5, U6.26 (GPA5)
/16-bits-6/GP6: P7.3, U6.27 (GPA6)
/16-bits-6/GP7: P7.1, U6.28 (GPA7)
/16-bits-6/GP8: P7.2, U6.1 (GPB0)
/16-bits-6/GP9: P7.4, U6.2 (GPB1)
/16-bits-6/GP10: P7.6, U6.3 (GPB2)
/16-bits-6/GP11: P7.8, U6.4 (GPB3)
/16-bits-6/GP12: P7.10, U6.5 (GPB4)
/16-bits-6/GP13: P7.12, U6.6 (GPB5)
/16-bits-6/GP14: P7.14, U6.7 (GPB6)
/16-bits-6/GP15: P7.16, U6.8 (GPB7)
/16-bits-6/INTA: U6.20 (INTA); also elsewhere on the board
/16-bits-7/GP0: P8.15, U7.21 (GPA0)
/16-bits-7/GP1: P8.13, U7.22 (GPA1)
/16-bits-7/GP2: P8.11, U7.23 (GPA2)
/16-bits-7/GP3: P8.9, U7.24 (GPS3)
/16-bits-7/GP4: P8.7, U7.25 (GPA4)
/16-bits-7/GP5: P8.5, U7.26 (GPA5)
/16-bits-7/GP6: P8.3, U7.27 (GPA6)
/16-bits-7/GP7: P8.1, U7.28 (GPA7)
/16-bits-7/GP8: P8.2, U7.1 (GPB0)
/16-bits-7/GP9: P8.4, U7.2 (GPB1)
/16-bits-7/GP10: P8.6, U7.3 (GPB2)
/16-bits-7/GP11: P8.8, U7.4 (GPB3)
/16-bits-7/GP12: P8.10, U7.5 (GPB4)
/16-bits-7/GP13: P8.12, U7.6 (GPB5)
/16-bits-7/GP14: P8.14, U7.7 (GPB6)
/16-bits-7/GP15: P8.16, U7.8 (GPB7)
/16-bits-7/INTA: U7.20 (INTA); also elsewhere on the board
/16-bits-8/GP0: P9.15, U8.21 (GPA0)
/16-bits-8/GP1: P9.13, U8.22 (GPA1)
/16-bits-8/GP2: P9.11, U8.23 (GPA2)
/16-bits-8/GP3: P9.9, U8.24 (GPS3)
/16-bits-8/GP4: P9.7, U8.25 (GPA4)
/16-bits-8/GP5: P9.5, U8.26 (GPA5)
/16-bits-8/GP6: P9.3, U8.27 (GPA6)
/16-bits-8/GP7: P9.1, U8.28 (GPA7)
/16-bits-8/GP8: P9.2, U8.1 (GPB0)
/16-bits-8/GP9: P9.4, U8.2 (GPB1)
/16-bits-8/GP10: P9.6, U8.3 (GPB2)
/16-bits-8/GP11: P9.8, U8.4 (GPB3)
/16-bits-8/GP12: P9.10, U8.5 (GPB4)
/16-bits-8/GP13: P9.12, U8.6 (GPB5)
/16-bits-8/GP14: P9.14, U8.7 (GPB6)
/16-bits-8/GP15: P9.16, U8.8 (GPB7)
/16-bits-8/INTA: U8.20 (INTA); also elsewhere on the board
GND: C2.2, C3.2, C4.2, C5.2, C6.2, C7.2, C8.2, P2.19, P2.20, P3.19, P3.20, P4.19, P4.20, P6.19, P6.20, P7.19, P7.20, P8.19, P8.20, P9.19, P9.20, U2.10 (VSS), U2.16 (A1), U2.17 (A2), U3.10 (VSS), U3.15 (A0), U3.17 (A2), U4.10 (VSS), U4.17 (A2), U5.10 (VSS), U5.15 (A0), U5.16 (A1), U6.10 (VSS), U6.16 (A1), U7.10 (VSS), U7.15 (A0), U8.10 (VSS); also elsewhere on the board

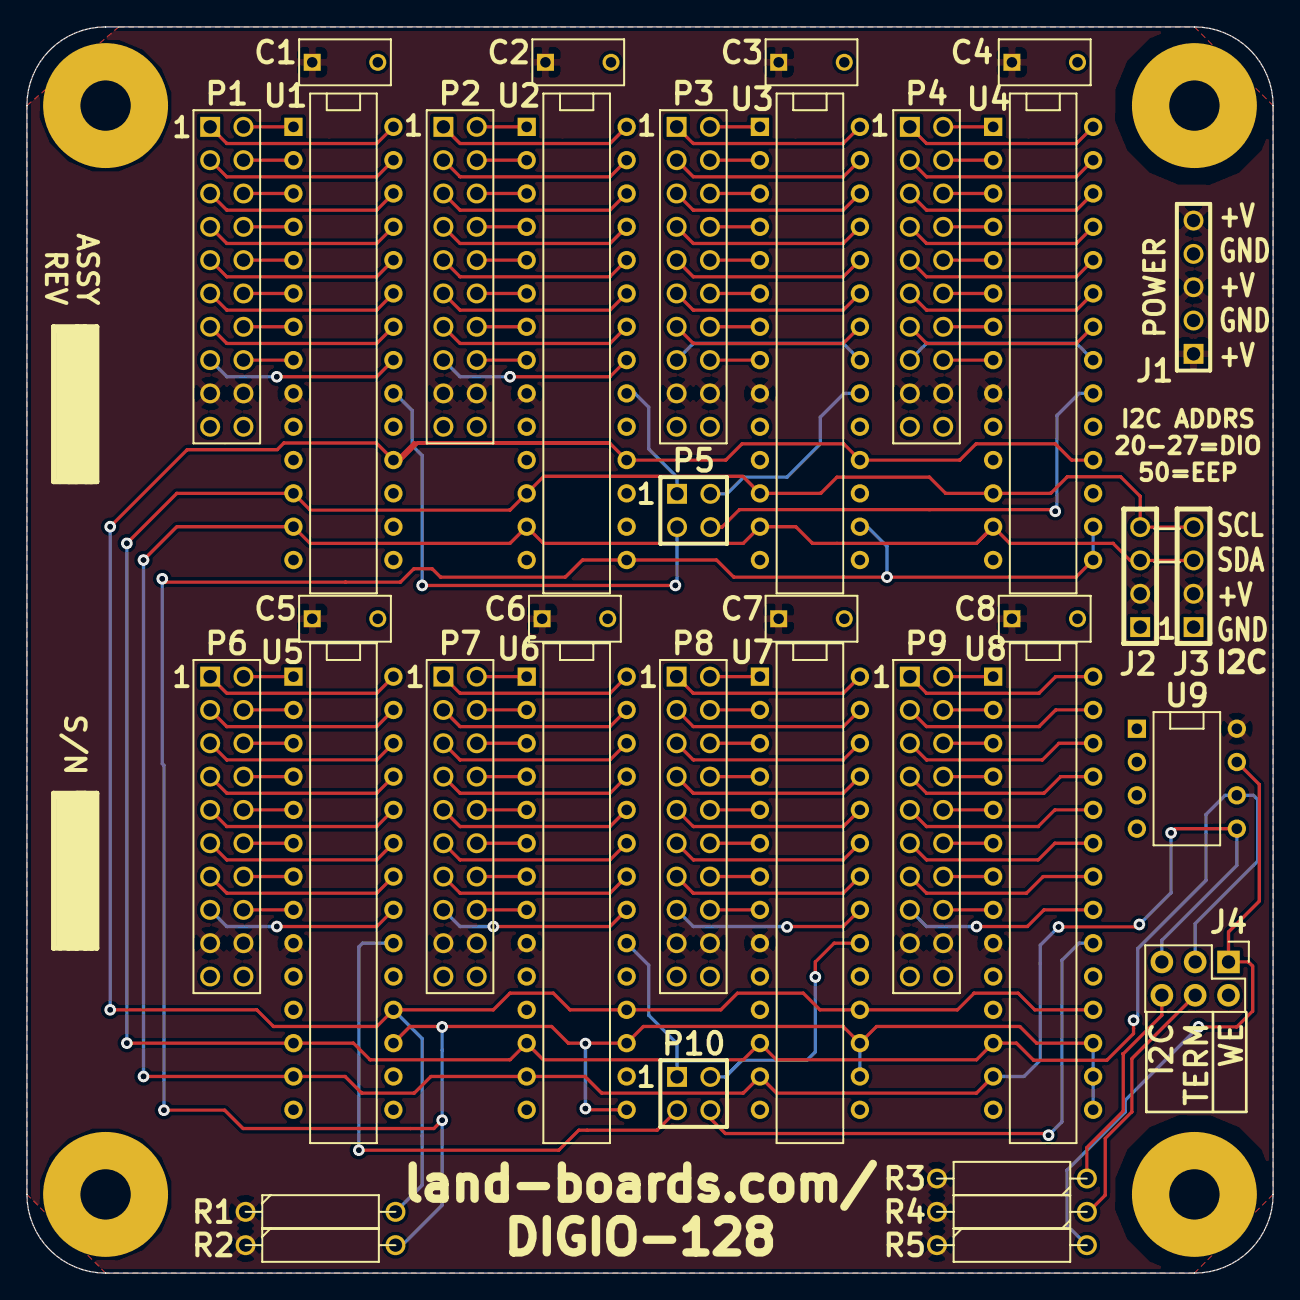
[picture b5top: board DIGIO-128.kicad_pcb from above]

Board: 2 copper layers, 95.0 x 95.0 mm, 42 parts (0 on the bottom side), 145 nets.
